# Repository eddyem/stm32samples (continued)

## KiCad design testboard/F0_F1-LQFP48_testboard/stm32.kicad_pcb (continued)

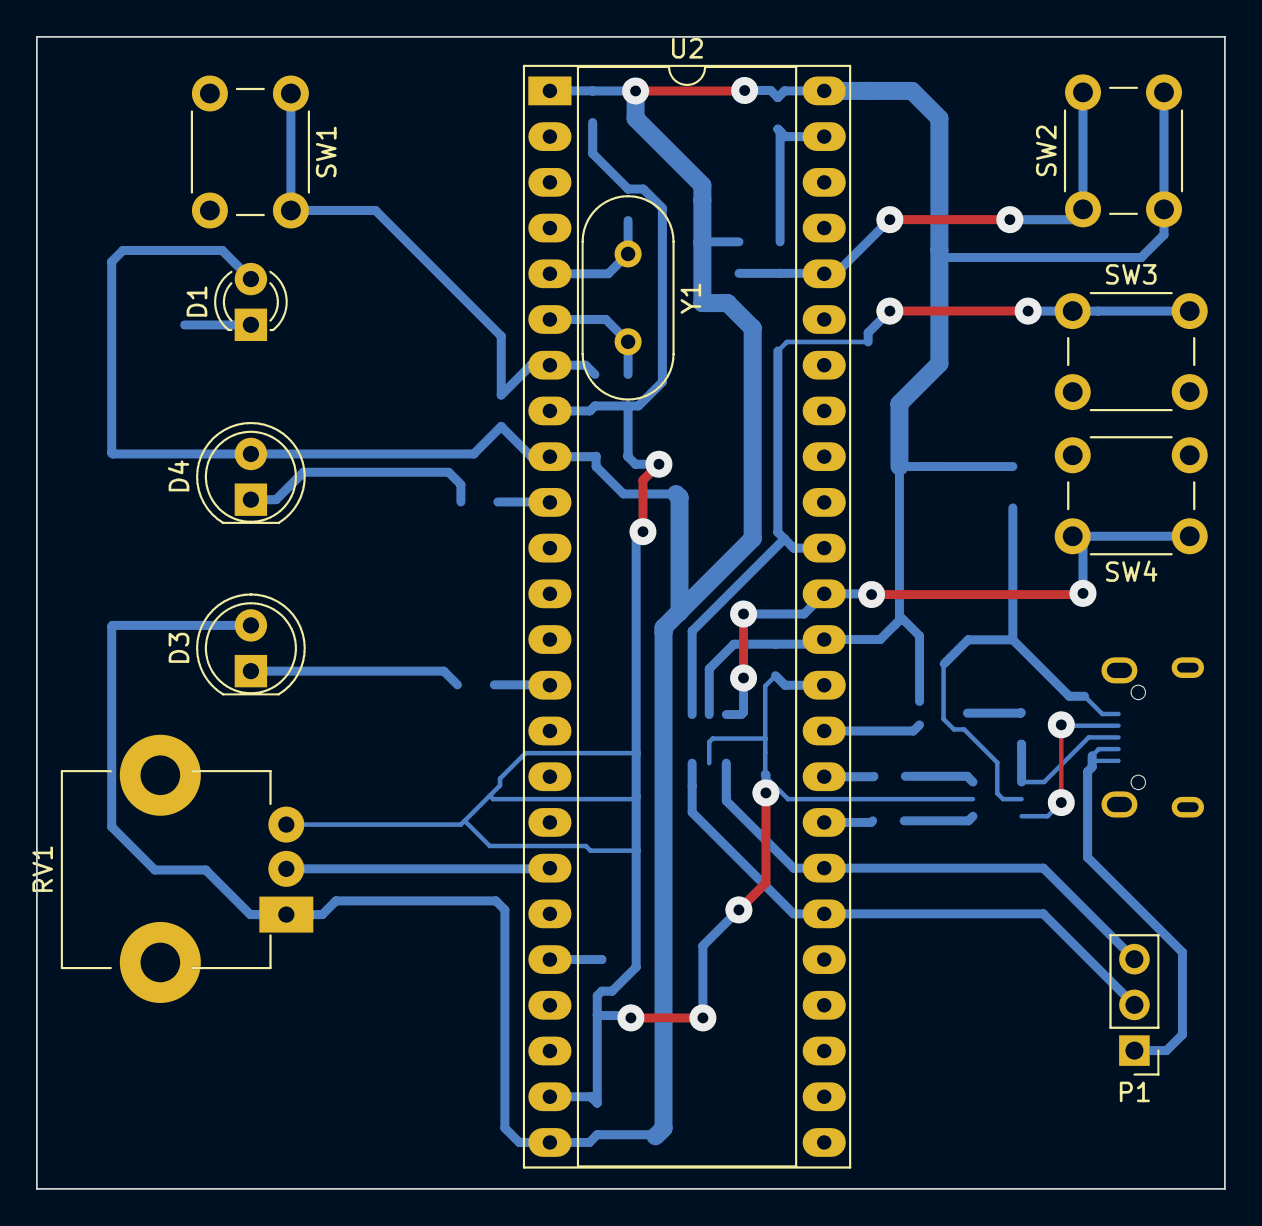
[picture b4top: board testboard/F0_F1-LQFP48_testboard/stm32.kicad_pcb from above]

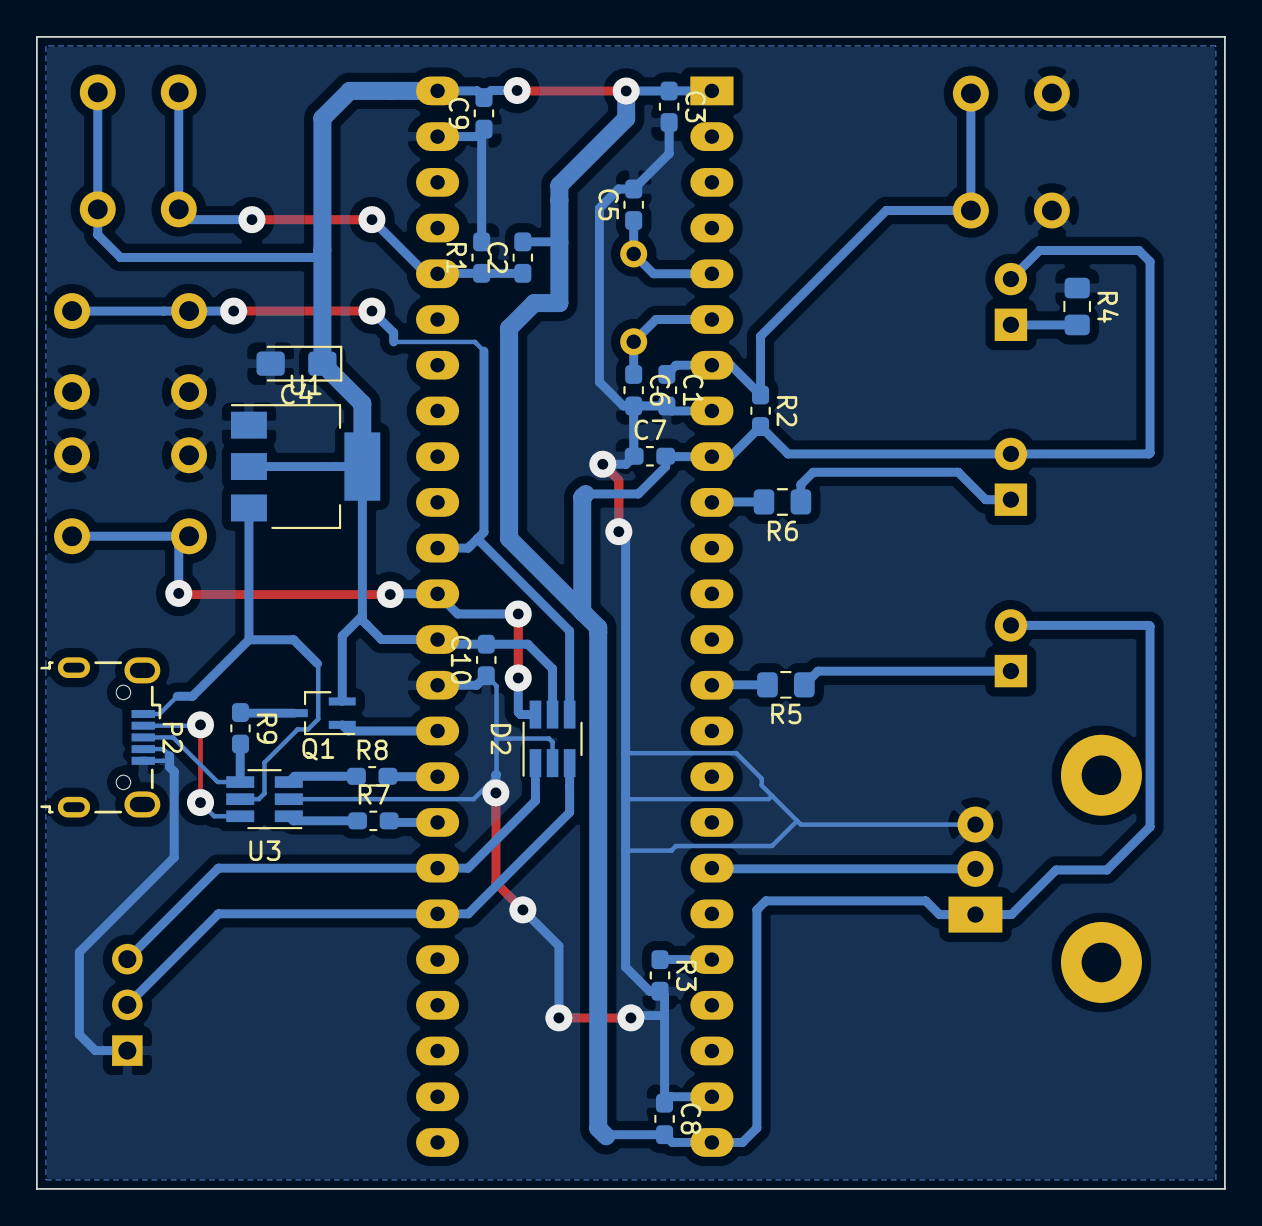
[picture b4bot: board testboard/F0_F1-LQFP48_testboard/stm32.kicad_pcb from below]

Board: 2 copper layers, 66.0 x 64.0 mm, 35 parts (24 on the bottom side), 26 nets.

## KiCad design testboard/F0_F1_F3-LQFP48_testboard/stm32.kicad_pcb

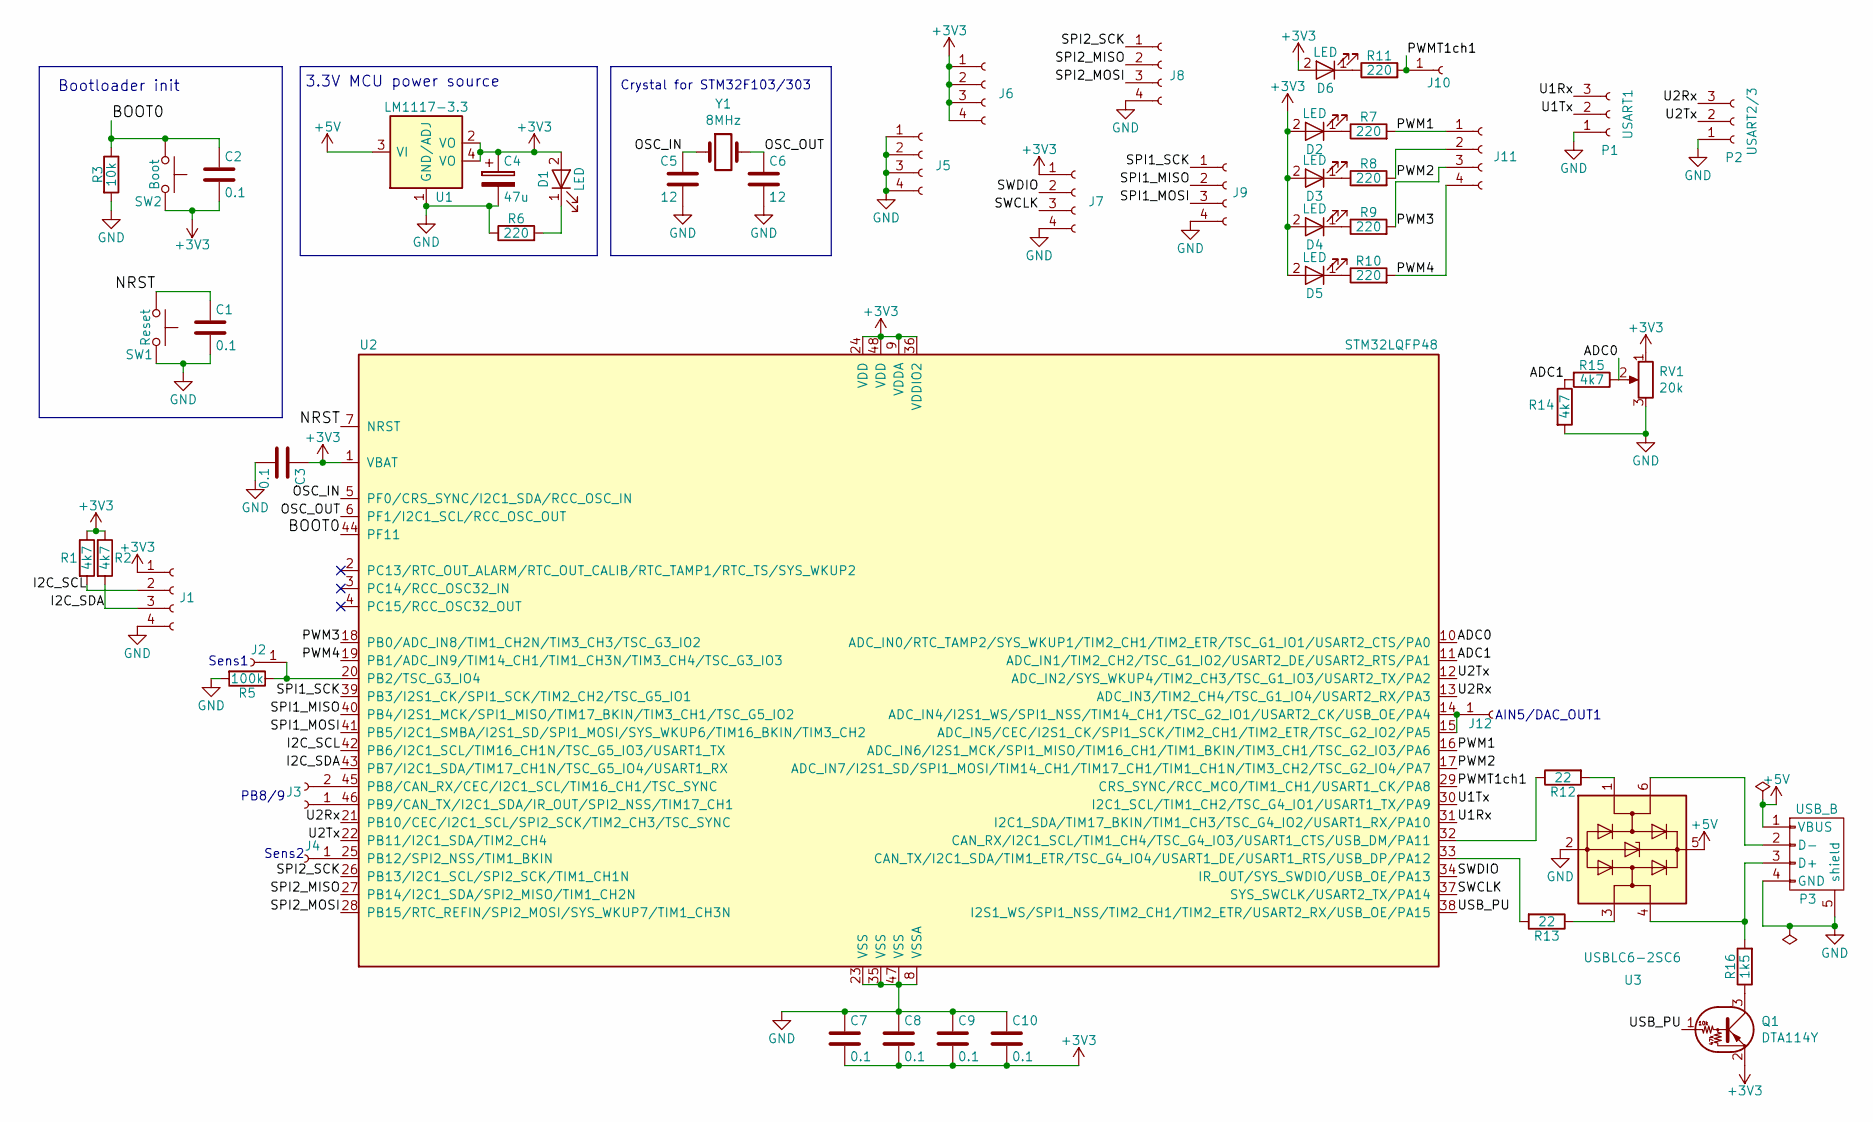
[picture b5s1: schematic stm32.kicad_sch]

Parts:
C1, C2, C3, C7, C8, C9, C10: 0.1; C_0603_1608Metric_Pad1.05x0.95mm_HandSolder
C4: 47u; CP_EIA-6032-28_Kemet-C_Pad2.25x2.35mm_HandSolder
C5, C6: 12; C_0603_1608Metric_Pad1.05x0.95mm_HandSolder
D1, D2, D3, D4, D5, D6: LED; LED_D3.0mm
J1, J5, J6, J7, J8, J9, J11: Conn_01x04_Female; PinSocket_1x04_P2.54mm_Vertical
J2, J4, J10, J12: Conn_01x01_Female; PinSocket_1x01_P2.54mm_Vertical
J3: Conn_01x02_Female; PinSocket_1x02_P2.54mm_Vertical
P1: USART1; PinSocket_1x03_P2.54mm_Vertical
P2: USART2/3; PinSocket_1x03_P2.54mm_Vertical
P3: USB_B; USB_B_OST_USB-B1HSxx_Horizontal
Q1: DTA114Y; SOT-323_SC-70_Handsoldering
R1, R2, R14, R15: 4k7; R_0805_2012Metric_Pad1.15x1.40mm_HandSolder
R3: 10k; R_0603_1608Metric_Pad1.05x0.95mm_HandSolder
R5: 100k; R_0603_1608Metric_Pad1.05x0.95mm_HandSolder
R6, R7, R8, R9, R10, R11: 220; R_0805_2012Metric_Pad1.15x1.40mm_HandSolder
R12, R13: 22; R_0603_1608Metric_Pad1.05x0.95mm_HandSolder
R16: 1k5; R_0603_1608Metric_Pad1.05x0.95mm_HandSolder
RV1: 20k; Potentiometer
SW1: Reset; SW_PUSH_6mm
SW2: Boot; SW_PUSH_6mm
U1: LM1117-3.3; SOT-223
U2: STM32LQFP48; DIP-48_W15.24mm_Socket_LongPads
U3: USBLC6-2SC6; SOT-23-6_Handsoldering
Y1: 8MHz; Crystal_HC49-U_Vertical

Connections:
+3V3: C2.2, C3.1, C4.1, C7.2, C8.2, C9.2, C10.2, D1.2 (A), D2.2 (A), D3.2 (A), D4.2 (A), D5.2 (A), D6.2 (A), J1.1, J6.1, J6.2, J6.3, J6.4, J7.1, Q1.2 (E), R1.1, R2.1, RV1.1, SW2.2, U1.2 (VO), U1.4 (VO), U2.1 (VBAT), U2.9 (VDDA), U2.24 (VDD), U2.36 (VDDIO2), U2.48 (VDD)
+5V: P3.1 (VBUS), U1.3 (VI), U3.5 (VBUS)
/ADC0: R15.1, RV1.2, U2.10 (ADC_IN0/RTC_TAMP2/SYS_WKUP1/TIM2_CH1/TI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)
/ADC1: R14.1, R15.2, U2.11 (ADC_IN1/TIM2_CH2/TSC_G1_IO2/USART2_DE/U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)
/BOOT0: C2.1, R3.1, SW2.1, U2.44 (PF11)
/I2C_SCL: J1.2, R1.2, U2.42 (PB6/I2C1_SCL/TIM16_CH1N/TSC_G5_IO3/USAR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)
/I2C_SDA: J1.3, R2.2, U2.43 (PB7/I2C1_SDA/TIM17_CH1N/TSC_G5_IO4/USAR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)
/NRST: C1.1, SW1.1, U2.7 (NRST)
/OSC_IN: C5.1, U2.5 (PF0/CRS_SYNC/I2C1_SDA/RCC_OSC_IN), Y1.1
/OSC_OUT: C6.1, U2.6 (PF1/I2C1_SCL/RCC_OSC_OUT), Y1.2
/PWM1: J11.1, R7.2, U2.16 (ADC_IN6/I2S1_MCK/SPI1_MISO/TIM16_CH1/TI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)
/PWM2: J11.2, R8.2, U2.17 (ADC_IN7/I2S1_SD/SPI1_MOSI/TIM14_CH1/TIM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)
/PWM3: J11.3, R9.2, U2.18 (PB0/ADC_IN8/TIM1_CH2N/TIM3_CH3/TSC_G3_I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)
/PWM4: J11.4, R10.2, U2.19 (PB1/ADC_IN9/TIM14_CH1/TIM1_CH3N/TIM3_CH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)
/PWMT1ch1: J10.1, R11.2, U2.29 (CRS_SYNC/RCC_MCO/TIM1_CH1/USART1_CK/PA8)
/SPI1_MISO: J9.2, U2.40 (PB4/I2S1_MCK/SPI1_MISO/TIM17_BKIN/TIM3_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)
/SPI1_MOSI: J9.3, U2.41 (PB5/I2C1_SMBA/I2S1_SD/SPI1_MOSI/SYS_WKU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)
/SPI1_SCK: J9.1, U2.39 (PB3/I2S1_CK/SPI1_SCK/TIM2_CH2/TSC_G5_IO1)
/SPI2_MISO: J8.2, U2.27 (PB14/I2C1_SDA/SPI2_MISO/TIM1_CH2N)
/SPI2_MOSI: J8.3, U2.28 (PB15/RTC_REFIN/SPI2_MOSI/SYS_WKUP7/TIM1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)
/SPI2_SCK: J8.1, U2.26 (PB13/I2C1_SCL/SPI2_SCK/TIM1_CH1N)
/SWCLK: J7.3, U2.37 (SYS_SWCLK/USART2_TX/PA14)
/SWDIO: J7.2, U2.34 (IR_OUT/SYS_SWDIO/USB_OE/PA13)
/U1Rx: P1.3, U2.31 (I2C1_SDA/TIM17_BKIN/TIM1_CH3/TSC_G4_IO2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)
/U1Tx: P1.2, U2.30 (I2C1_SCL/TIM1_CH2/TSC_G4_IO1/USART1_TX/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)
/U2Rx: P2.3, U2.13 (ADC_IN3/TIM2_CH4/TSC_G1_IO4/USART2_RX/P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), U2.21 (PB10/CEC/I2C1_SCL/SPI2_SCK/TIM2_CH3/TSC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)
/U2Tx: P2.2, U2.12 (ADC_IN2/SYS_WKUP4/TIM2_CH3/TSC_G1_IO3/U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), U2.22 (PB11/I2C1_SDA/TIM2_CH4)
/USB_PU: Q1.1 (B), U2.38 (I2S1_WS/SPI1_NSS/TIM2_CH1/TIM2_ETR/USAR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)
GND: C1.2, C3.2, C4.2, C5.2, C6.2, C7.1, C8.1, C9.1, C10.1, J1.4, J5.1, J5.2, J5.3, J5.4, J7.4, J8.4, J9.4, P1.1, P2.1, P3.4 (GND), P3.5 (shield), R3.2, R5.2, R6.1, R14.2, RV1.3, SW1.2, U1.1 (GND/ADJ), U2.8 (VSSA), U2.23 (VSS), U2.35 (VSS), U2.47 (VSS), U3.2 (GND)
unnamed: D1.1 (K), R6.2
unnamed: D2.1 (K), R7.1
unnamed: D3.1 (K), R8.1
unnamed: D4.1 (K), R9.1
unnamed: D5.1 (K), R10.1
unnamed: D6.1 (K), R11.1
unnamed: J2.1, R5.1, U2.20 (PB2/TSC_G3_IO4)
unnamed: J3.1, U2.46 (PB9/CAN_TX/I2C1_SDA/IR_OUT/SPI2_NSS/TIM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)
unnamed: J3.2, U2.45 (PB8/CAN_RX/CEC/I2C1_SCL/TIM16_CH1/TSC_S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)
unnamed: J4.1, U2.25 (PB12/SPI2_NSS/TIM1_BKIN)
unnamed: J12.1, U2.14 (ADC_IN4/I2S1_WS/SPI1_NSS/TIM14_CH1/TSC_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), U2.15 (ADC_IN5/CEC/I2S1_CK/SPI1_SCK/TIM2_CH1/T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)
unnamed: P3.2 (D-), U3.6 (I/O1)
unnamed: P3.3 (D+), R16.2, U3.4 (I/O2)
unnamed: Q1.3 (C), R16.1
unnamed: R13.1, U3.3 (I/O2)
unnamed: R13.2, U2.33 (CAN_TX/I2C1_SDA/TIM1_ETR/TSC_G4_IO4/USA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)

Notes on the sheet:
Sens1
3.3V MCU power source
Crystal for STM32F103/303
PB8/9
AIN5/DAC_OUT1
Bootloader init
Sens2

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
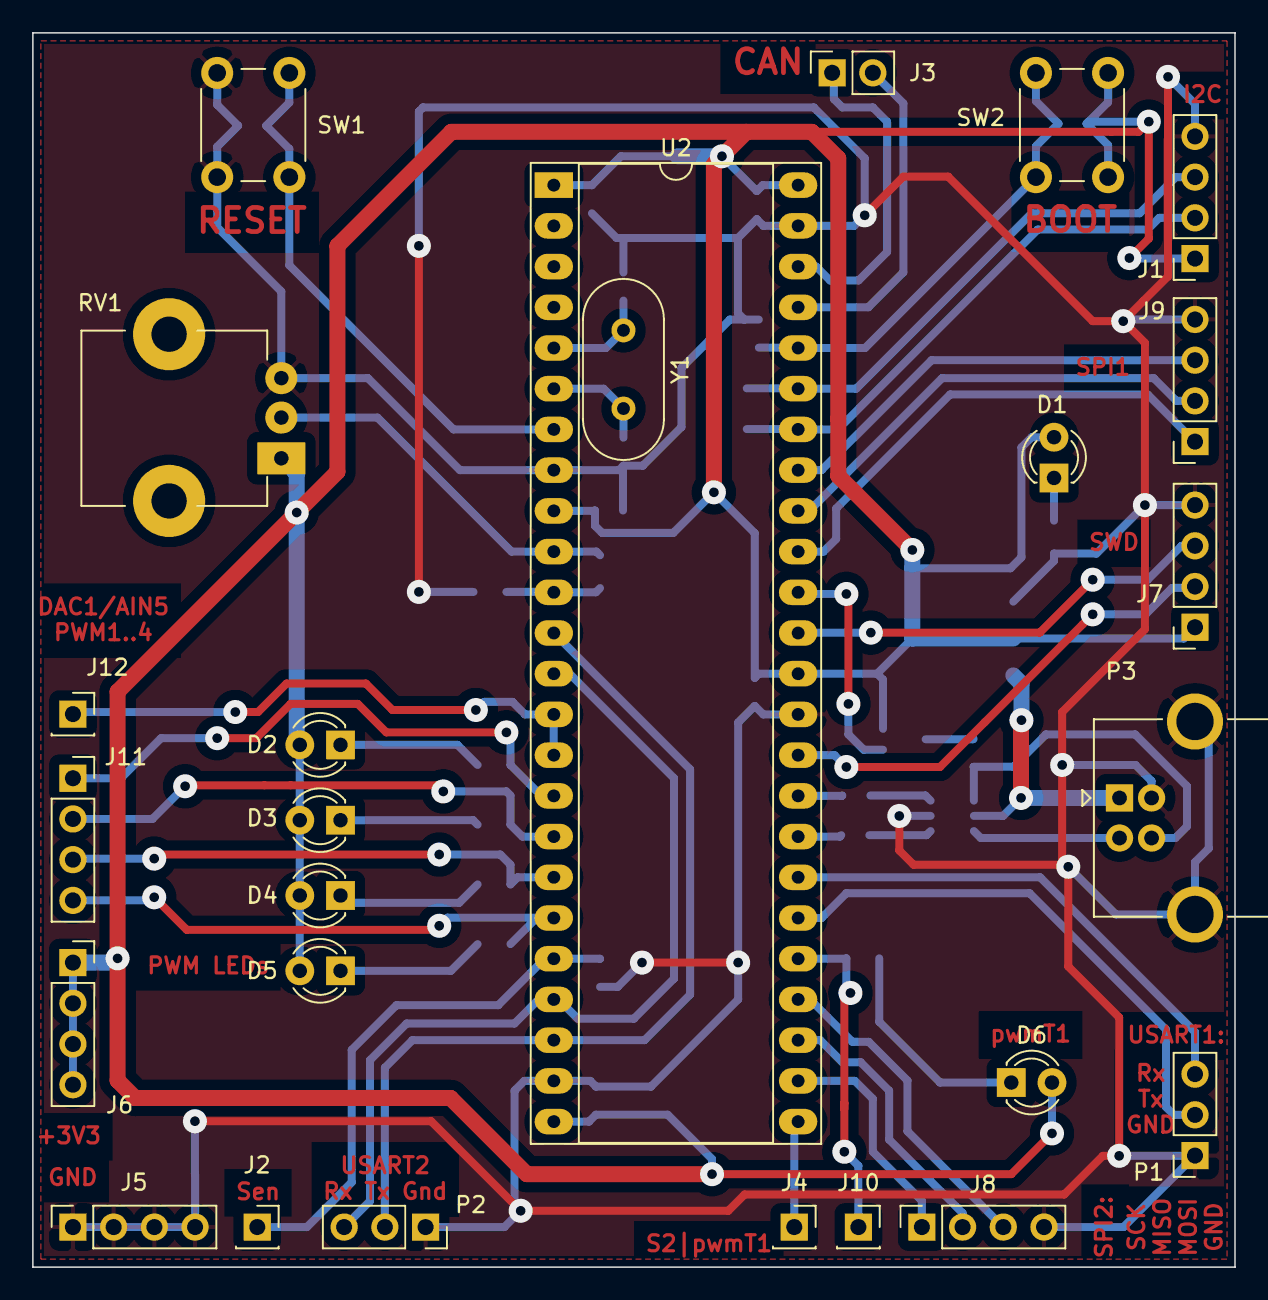
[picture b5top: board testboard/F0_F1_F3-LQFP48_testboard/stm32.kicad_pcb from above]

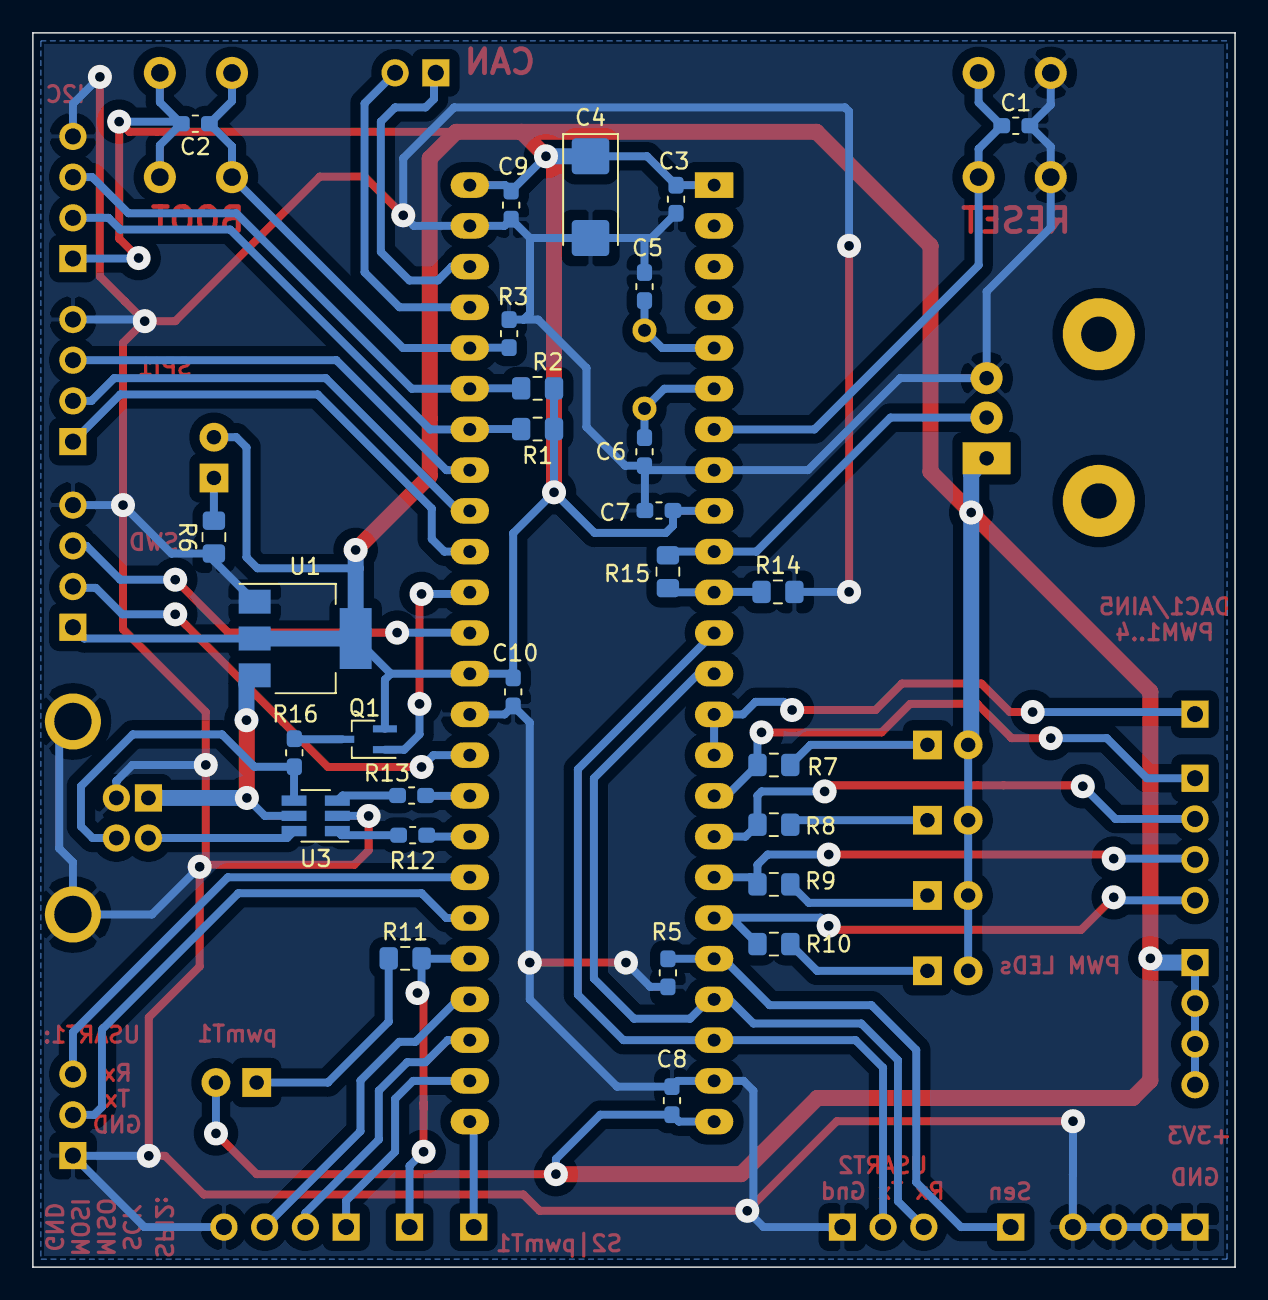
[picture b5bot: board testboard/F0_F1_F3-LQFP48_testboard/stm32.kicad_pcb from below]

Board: 2 copper layers, 75.0 x 77.0 mm, 54 parts (28 on the bottom side), 47 nets.
